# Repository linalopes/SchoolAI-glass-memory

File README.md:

# Glass Memory

A memory game played with the hands, on glass.

Five MDF hands sit on a transparent pane. Four of them hold a lamp. The fifth is Start. A small LED matrix waits, showing a single word. Place a hand on Start, watch the lamps light a sequence, then repeat that sequence by placing your hands on the other four. Each correct round adds one more step. A wrong direction, or a pause that lasts too long, ends the game and returns the panel to waiting.

The electronics stay visible: TRRS cables run across the glass, a custom controller board sits beside the display, and the lamps switch through a relay module. Nothing on the matrix ever names a direction. The sequence exists only as light, then as remembered gesture.

https://github.com/user-attachments/assets/acf82029-6c34-4761-a3db-518c1ffbd78a

---

## How it works

The visitor sees a glass pane with five hand-shaped stations, a red 32×8 LED matrix, and four lamps.

1. The matrix shows **START**.
2. A hand over the Start station begins a game. Start does not light a lamp.
3. The matrix counts **3 · 2 · 1**, then shows the round length as a number.
4. The computer plays the sequence on the four direction lamps only. The display stays blank during playback and never reveals UP, DOWN, LEFT, or RIGHT as text.
5. The matrix shows **GO**. The visitor repeats the sequence on the four direction hands, one press at a time, releasing each hand before the next.
6. A complete correct round shows **OK**. The sequence grows by one random direction and the next round begins.
7. A wrong hand shows **WR**. Taking too long to press, or holding a press too long, shows **TO**. The matrix then shows the number of completed rounds and returns to **START**.

Repeated presses of the same direction count as separate events, as long as the hand is lifted in between. Only Start is accepted while idle; only the four directions are accepted during a turn.

`Start → countdown → watch lamps → GO → repeat → OK → longer sequence`

---

## System overview

```text
Five analog sensors (START, UP, DOWN, LEFT, RIGHT)
        ↓  TRRS cables + adapter boards
Arduino Pro Micro controller
        ↓
Game logic  (sequence, input events, EEPROM calibration)
   ↙                    ↘
MAX7219 matrix         4-channel relay module
(text / numbers)               ↓
                         Direction lamps
```

The controller reads five analog sensor channels, decides when a hand is present, and either plays a lamp sequence or checks the player’s reply. Calibration values live in EEPROM and are loaded at boot; the game firmware does not rewrite them.

---

## Hardware

The running firmware and the KiCad controller project both target a **SparkFun Pro Micro C** (ATmega32U4, [product 15795](https://www.sparkfun.com/products/15795)), socketed on the custom board.

The schematic title block still says “ESP32-S3 controller”. That comment is leftover. The symbol, footprint, pin map, and firmware all use the Pro Micro.

| Role            | What is in this repo                                                                       | Purpose                                     |
| --------------- | ------------------------------------------------------------------------------------------ | ------------------------------------------- |
| Controller      | SparkFun Pro Micro C on the [glass-memory](kicad%20files/glass-memory/) PCB                | Runs calibration or game firmware           |
| Sensor jacks    | Five **PJ-320A** TRRS sockets (START, UP, DOWN, LEFT, RIGHT)                               | Detachable cable to each hand               |
| Sensor adapters | Five [sensor-trrs-adapter-pj320a](kicad%20files/sensor-trrs-adapter-pj320a/) boards        | PJ-320A jack to a 1×4 sensor header         |
| Sensors         | Five analog channels; 4-pin modules with **A0 / D0 / GND / VCC** on the adapter silkscreen | Detect a hand over each station             |
| Display         | External **MAX7219** 4-in-1 matrix (`FC16_HW`, 4 devices → 32×8)                           | Status text and numbers                     |
| Relays          | External **4-channel relay module**, active LOW                                            | Switch the four direction lamps             |
| Power           | 2-pin screw terminal **J8**, “5V Power Source” (pin 1 GND, pin 2 +5V)                      | 5 V rail shared with the Pro Micro `5V` pin |
| Mechanics       | Laser-cut hands / board, 3D-printed hand support and matrix bezel                          | Physical stations on the glass              |

The exact sensor part number is not named in the repository. Firmware comments treat the readings as optical (a slow “ambient optical drift” tracker). The adapter exposes both analog (**A0** / `AO`) and digital (**D0** / `DO`) pins; **only analog is used** by the firmware.

The installation photograph shows filament lamps at the four direction stations. This repository does not document lamp voltage or mains wiring. The relay stage switches those loads; any mains work must follow appropriate electrical safety practice.

### Controller pin map

Verified in both [glass-memory-game.ino](glass-memory-game/glass-memory-game.ino) and [glass-memory-calibration-eeprom.ino](glass-memory-calibration-eeprom/glass-memory-calibration-eeprom.ino), and matched on the Pro Micro footprint in the PCB.

| Function          | Pin |
| ----------------- | --- |
| START sensor      | A10 |
| UP sensor         | A9  |
| DOWN sensor       | A8  |
| LEFT sensor       | A0  |
| RIGHT sensor      | A7  |
| Relay IN1 (UP)    | D5  |
| Relay IN2 (DOWN)  | D4  |
| Relay IN3 (LEFT)  | D3  |
| Relay IN4 (RIGHT) | D2  |
| MAX7219 DIN       | D15 |
| MAX7219 CS        | D14 |
| MAX7219 CLK       | D16 |

Relays are **active LOW** (`RELAY_ON = LOW`). START has no relay.

---

## Custom electronics

Two KiCad 10 projects ship with production gerbers. They are the current hardware, not a paper design only.

### Controller — [kicad files/glass-memory](kicad%20files/glass-memory/)

Silkscreen: *Glass Memory Controller 2026 - v1.0*. Outline **60 × 80 mm** with 2 mm corner radii (`Edge.Cuts` from 50.5,45 to 110.5,125), plus M3 holes.

The board is a hub:

- **U1** — socketed Pro Micro C
- **J1–J5** — PJ-320A TRRS jacks labeled START, UP, DOWN, LEFT, RIGHT
- **J6** — Phoenix MKDS 6-pin screw terminal, “RELAY 4 module”: `RELAY_IN4`, `RELAY_IN3`, `RELAY_IN2`, `RELAY_IN1`, `GND`, `+5V` (pins 1–6)
- **J7** — 5-pin header, “MAX7219 module”: `+5V`, `GND`, `DIN`, `CS`, `CLK` (pins 1–5)
- **J8** — Phoenix MKDS 2-pin screw terminal for 5 V in (pin 1 `GND`, pin 2 `+5V`). There is no on-board regulator; U1 `RAW` is unconnected.

Gerbers: [kicad files/glass-memory/production/](kicad%20files/glass-memory/production/).

### Sensor adapter — [kicad files/sensor-trrs-adapter-pj320a](kicad%20files/sensor-trrs-adapter-pj320a/)

Silkscreen: *TRRS PJ-320A 1×4 ADAPTER*. Schematic comment: *PJ-320A TRRS jack → 1×4 female header*.

One adapter sits at each hand. Board size in the gerber job is **24.6 × 15.1 mm**. The 1×4 header (J1) is:

| Pin | Net   | Back silk |
| --- | ----- | --------- |
| 1   | `AO`  | `A0`      |
| 2   | `DO`  | `D0`      |
| 3   | `GND` | `GND`     |
| 4   | `3V3` | `VCC`     |

Gerbers: [kicad files/sensor-trrs-adapter-pj320a/production/](kicad%20files/sensor-trrs-adapter-pj320a/production/).

---

## Sensor cabling

TRRS (PJ-320A, 3.5 mm 4-pole) is used so each hand can be a remote node: power, ground, and analog return travel in one detachable cable from the glass to the hub.

The table below follows the **PCB copper** on both boards (and the matching gerbers), using the custom [TRRS-PJ-320A](kicad%20files/glass-memory/TRRS-PJ-320A.pretty/TRRS-PJ-320A.kicad_mod) footprint labels.

| TRRS contact | Symbol pin | Controller PCB | Adapter PCB                    |
| ------------ | ---------- | -------------- | ------------------------------ |
| Sleeve       | S / pad 1  | `GND`          | `GND`                          |
| Tip          | T / pad 2  | not connected  | `DO` (digital out)             |
| Ring 1       | R1 / pad 3 | `+5V`          | net labeled `3V3` / silk `VCC` |
| Ring 2       | R2 / pad 4 | analog `*_A0`  | `AO`                           |

The controller uses **three** conductors. Tip is unused on the hub, so the sensor digital output is not read.

**Ambiguities to be aware of:**

1. The hub schematic *labels* next to the jacks appear to swap Sleeve and Ring 1 relative to the PCB (`+5V` on Sleeve, `GND` on Ring 1). The PCB, gerbers, and adapter all agree the other way: Sleeve = ground, Ring 1 = power. This README follows the copper.
2. The hub puts **+5 V** on Ring 1. The adapter net for that same contact is named **3V3**. Confirm the sensor module’s supply rating before applying power. TODO: document the intended sensor supply and module part number.

---

## Sensors

Five analog inputs, mapped as START / UP / DOWN / LEFT / RIGHT.

Each reading is an average of four ADC samples (first conversion after a channel change is discarded), then exponentially smoothed (`75%` previous + `25%` new). Presence is not a raw threshold. After calibration, a score of `0%` is the resting baseline and `100%` is the stored hand sample:

- press when score ≥ **50%** and that sensor beats the next by **10%**
- release when score < **30%**
- a press must stay stable **80 ms**; after release, the allowed sensors must stay neutral **120 ms** before the next press can arm

During a player turn the RAM baseline slowly follows ambient optical drift (every 100 ms, only while a sensor is well below the press threshold). EEPROM is not updated. The useful span is not allowed to collapse below a live delta of 20.

The game firmware latches one accepted sensor until *that same* sensor releases, so LEFT → LEFT is two events if the hand lifts in between.

---

## Calibration

Firmware: [glass-memory-calibration-eeprom/glass-memory-calibration-eeprom.ino](glass-memory-calibration-eeprom/glass-memory-calibration-eeprom.ino)

Optical rest levels shift with light and mounting. Calibration measures a clear-pane baseline and a hand sample per station, stores both in EEPROM, and is a **separate sketch** from the game.

Upload this sketch to the Pro Micro (Arduino IDE, board: SparkFun Pro Micro / ATmega32U4). Serial is 115200 baud. Calibration still runs if Serial is not open.

### Automatic flow

The matrix and Serial walk through the same sequence:

```text
CAL
CLEAR   → keep the complete sensor area clear → 3 · 2 · 1 → baseline
START   → prepare a hand over START → 3 · 2 · 1 → hand sample
UP      → same
DOWN
LEFT
RIGHT
DONE    → values written to EEPROM
TEST    → live sensor + relay check
```

Each measurement averages **120** analog samples with **4 ms** between samples. For every sensor the sketch stores:

- `baseline` — mean of the clear-pane capture
- `hand` — mean of that station’s hand capture
- `delta` — `hand − baseline`

Min/max during each capture are printed for noise diagnosis. The EEPROM record is:

```text
magic 0x474D ("GM") · version 1 · baseline[5] · hand[5] · checksum
```

The write is read back immediately (`EEPROM SAVE: OK` or `ERROR`). Values persist across power cycles. Resetting the board runs the whole calibration again.

### Live test

After SAVE, the sketch stays in TEST. An accepted sensor lights its relay (except START) and draws a marker on the matrix (center / top / bottom / left / right edge). Serial prints all five `filtered/score%` values twice a second, tagged `[ACTIVE]`, `[CAND]`, or `[--]`.

Send `P` on Serial to reprint the calibration table.

Then upload the game sketch. Do not recalibrate unless the mounting or lighting changed.

---

## Firmware

Current game firmware: [glass-memory-game/glass-memory-game.ino](glass-memory-game/glass-memory-game.ino) (**Game V4**).

It is not the calibration sketch. If EEPROM magic, version, checksum, or any sensor delta is invalid (`|delta| < 2`), the matrix shows **CAL** and the board waits there.

V4 responsibilities:

- load calibration; never write EEPROM
- continuous analog filter; slow RAM baseline tracking
- PRESS → LATCH → RELEASE → NEUTRAL → ARMED input machine
- idle wait on START only
- random direction sequence (UP/DOWN/LEFT/RIGHT), length 1…32
- lamp-only playback (`700 ms` on, `250 ms` gap)
- per-press timeout `10 s`, release timeout `5 s`
- player lamp feedback while the accepted hand is present (`PLAYER_LAMP_FEEDBACK`; set to `0` only for A/B diagnostics — computer playback always uses the lamps)
- serial debug at 115200 when `DEBUG_SERIAL` is 1

---

## Display

A four-module MAX7219 chain (`MD_MAX72XX::FC16_HW`, intensity 3). Firmware maps pixels with **X reversed** and **Y normal** (`physicalCol = 31 − logicalCol`) so the physical panel matches the intended left-to-right text.

| When                | Matrix shows             |
| ------------------- | ------------------------ |
| Idle                | `START`                  |
| Missing calibration | `CAL` (then halt)        |
| New game            | `3` `2` `1`              |
| Before playback     | round length as a number |
| Sequence playback   | blank                    |
| Player turn         | `GO`                     |
| Round correct       | `OK`                     |
| Wrong hand          | `WR`, then the score     |
| Timeout             | `TO`, then the score     |

The 3D-printed [MAX7219 bezel](3D%20print%20files/glass_memory_max7219_beze.scad) is a rear-entry frame for a 32×8 assembly (~131 mm wide including inter-module gaps).

---

## Relays and lights

Four channels, active LOW, mapped as IN1–IN4 above. During computer playback each step turns on exactly one lamp. During the player turn the matching lamp stays on while that hand remains present (if player feedback is enabled). START never drives a relay. All relays are forced off between steps, on error, and in idle.

---

## Building the system

1. Fabricate the controller and one adapter per sensor (gerbers are under each project’s `production/` folder).
2. Seat the Pro Micro in the U1 socket.
3. Wire the MAX7219 module to J7 and the 4-channel relay module to J6.
4. At each hand, plug the 4-pin sensor into the adapter header and a TRRS cable from the adapter jack to the matching hub jack.
5. Supply 5 V on J8. Confirm sensor supply (see cabling note on +5 V vs `3V3`).
6. Upload **calibration**, clear the pane, then present a hand at each named station.
7. In TEST, confirm each direction lights the intended lamp and that Serial scores separate cleanly.
8. Upload **game** firmware. If the matrix shows `CAL`, calibration is missing or invalid — go back to step 6.
9. From idle, start a game and walk a short sequence before hanging the piece.

Laser-cut hands and board: [laser cut files](laser%20cut%20files/) (72 dpi SVG, plus `board.af`). 3D-printed hand support and matrix bezel: [3D print files](3D%20print%20files/). The hand OpenSCAD file is generated from the 72 dpi SVG contour (hand size ~60 × 80 mm, 3 mm MDF).

---

## Repository structure

```text
.
├── README.md
├── glass-memory.webp                          installation photograph
├── glass-memory.mp4                           installation video
├── glass-memory-game/                         game firmware V4
│   └── glass-memory-game.ino
├── glass-memory-calibration-eeprom/           EEPROM calibration + live TEST
│   └── glass-memory-calibration-eeprom.ino
├── kicad files/
│   ├── glass-memory/                          controller PCB + gerbers
│   └── sensor-trrs-adapter-pj320a/            per-sensor TRRS adapter + gerbers
├── laser cut files/                           hands, start hand, board (SVG / Affinity)
└── 3D print files/                            hand support + MAX7219 bezel
```

KiCad local history and zip backups exist under the hardware folders; they are snapshots, not the working design.

---

## Troubleshooting

Drawn from the diagnostic paths that actually exist in firmware.

| Symptom                                              | What the firmware is telling you                                                                                               |
| ---------------------------------------------------- | ------------------------------------------------------------------------------------------------------------------------------ |
| Matrix stuck on `CAL`                                | EEPROM magic/version/checksum failed, or a stored delta is ~0. Run calibration and confirm `EEPROM SAVE: OK`.                  |
| Start does nothing, directions work (or the reverse) | Wrong TRRS jack, or the allowed-sensor mask: idle listens only to START; play listens only to the four directions.             |
| One press counted twice, or LEFT cannot follow LEFT  | The hand never returned below the 30% release score for 120 ms. Check Serial scores in the calibration TEST.                   |
| Wrong lamp or two lamps                              | Winner margin is 10%. If two sensors both cross 50%, no winner is taken. Recalibrate with only one hand in place.              |
| Resting scores creep up after a while                | Expected: game tracks ambient drift in RAM only. If a real touch no longer reaches ~100%, recalibrate.                         |
| Display text mirrored                                | Firmware already reverses X for this panel. If it looks wrong, the module order or `FC16_HW` wiring does not match this build. |
| Relays on when they should be off                    | Modules are active LOW. Confirm the board is not treating IN as active HIGH.                                                   |
| `TO` during play                                     | 10 s to make the next press, or 5 s to release.                                                                                |
| Calibration deltas tiny                              | Baseline and hand samples were too similar. Repeat CLEAR with the pane empty, then place the hand fully over that station.     |

Serial (both sketches, 115200) prints per-sensor scores when debug is on. Calibration TEST is the right place to watch `base` / `hand` / `delta` / `noise`.

---

## Software requirements

- Arduino IDE (or any environment that can flash a Pro Micro / ATmega32U4)
- Libraries referenced by `#include`: **MD_MAX72xx**, **SPI**, **EEPROM** (SPI and EEPROM are Arduino core libraries). No versions are pinned in this repo.
- **KiCad 10** (schematic `generator_version "10.0"`)
- **OpenSCAD**, if regenerating the 3D parts

---

## Glass Memory web app

This repository does not contain a web app, simulator, or networked companion. The installation runs entirely on the Pro Micro.

TODO: link a companion app here if it lives in another repo.

---

## About the project

Glass Memory is an embodied memory game: instructions arrive as lamps on glass, and the reply is a sequence of hands. The matrix is deliberately mute about direction. What you remember is a path of gestures, not a string of arrows.

The work sits in physical computing — analog optical sensing, a visible cable plant, calibration as a ritual of settling the pane to a room — rather than a hidden black-box kiosk.

PCB silkscreen: *heavily inspired by Nathan Rabinovitch*. No exhibition history is recorded in this repository.

---

## Credits

- **Lina Lopes** — School of Tomorrow's AI (controller and adapter silkscreen, 2026 v1.0)
- Inspired by **Nathan Rabinovitch**

TODO: license. No `LICENSE` file is present in this repository.

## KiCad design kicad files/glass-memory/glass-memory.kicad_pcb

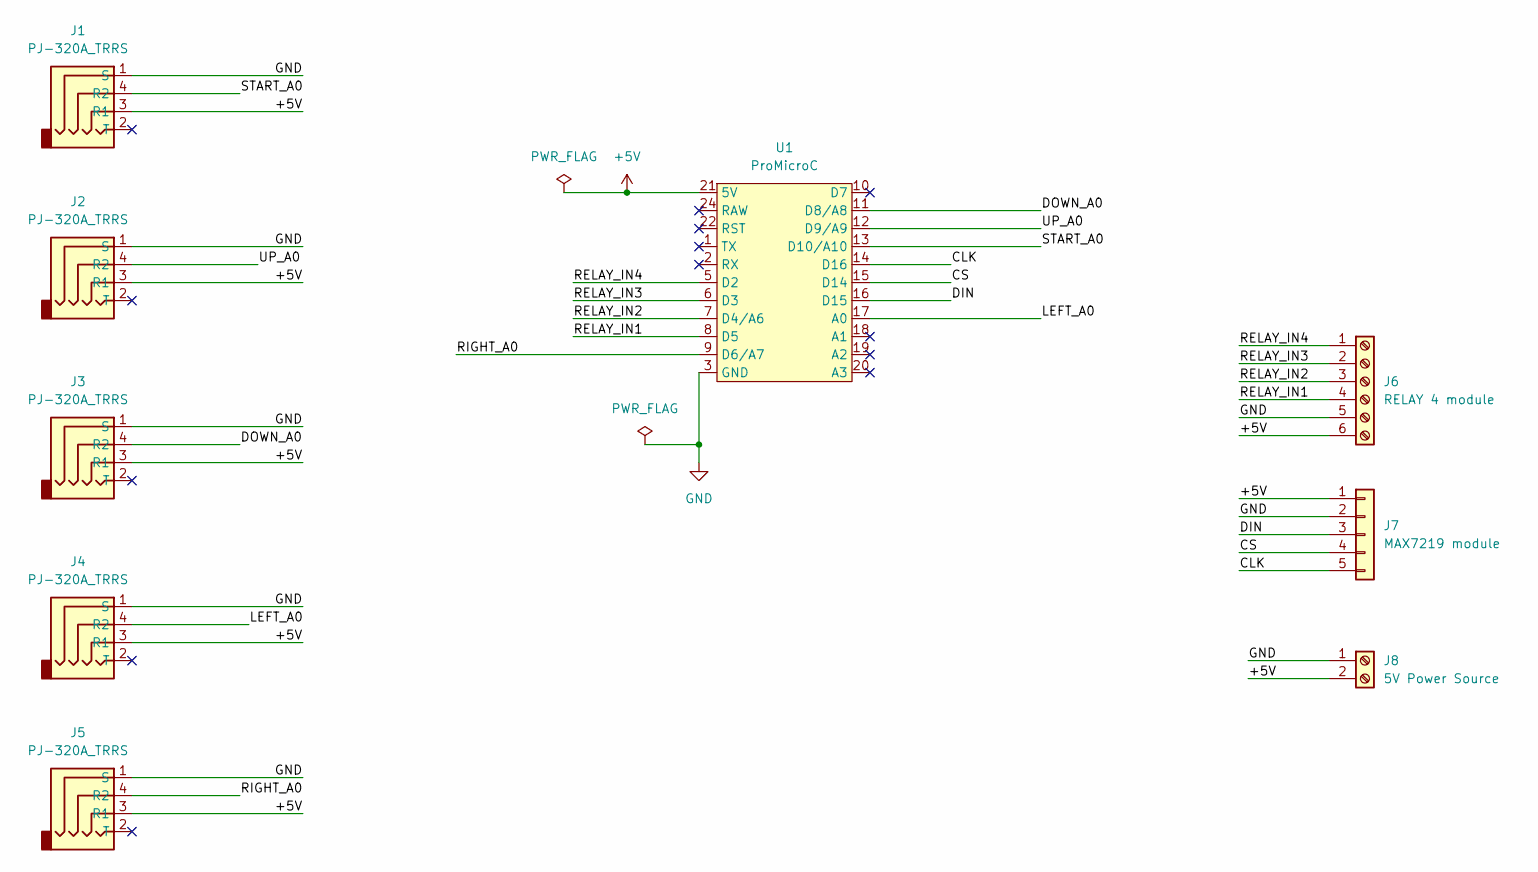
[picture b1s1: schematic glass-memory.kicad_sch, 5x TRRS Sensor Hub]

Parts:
J1, J2, J3, J4, J5: PJ-320A_TRRS; TRRS-PJ-320A
J6: RELAY 4 module; TerminalBlock_Phoenix_MKDS-1,5-6-5.08_1x06_P5.08mm_Horizont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
J7: MAX7219 module; PinHeader_1x05_P2.54mm_Vertical
J8: 5V Power Source; TerminalBlock_Phoenix_MKDS-1,5-2-5.08_1x02_P5.08mm_Horizont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
U1: ProMicroC; ProMicroC-socketed

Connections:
+5V: J1.3 (R1), J2.3 (R1), J3.3 (R1), J4.3 (R1), J5.3 (R1), J6.6, J7.1, J8.2, U1.21 (5V)
/CLK: J7.5, U1.14 (D16)
/CS: J7.4, U1.15 (D14)
/DIN: J7.3, U1.16 (D15)
/DOWN_A0: J3.4 (R2), U1.11 (D8/A8)
/LEFT_A0: J4.4 (R2), U1.17 (A0)
/RELAY_IN1: J6.4, U1.8 (D5)
/RELAY_IN2: J6.3, U1.7 (D4/A6)
/RELAY_IN3: J6.2, U1.6 (D3)
/RELAY_IN4: J6.1, U1.5 (D2)
/RIGHT_A0: J5.4 (R2), U1.9 (D6/A7)
/START_A0: J1.4 (R2), U1.13 (D10/A10)
/UP_A0: J2.4 (R2), U1.12 (D9/A9)
GND: J1.1 (S), J2.1 (S), J3.1 (S), J4.1 (S), J5.1 (S), J6.5, J7.2, J8.1, U1.3 (GND), U1.4 (GND), U1.23 (GND)

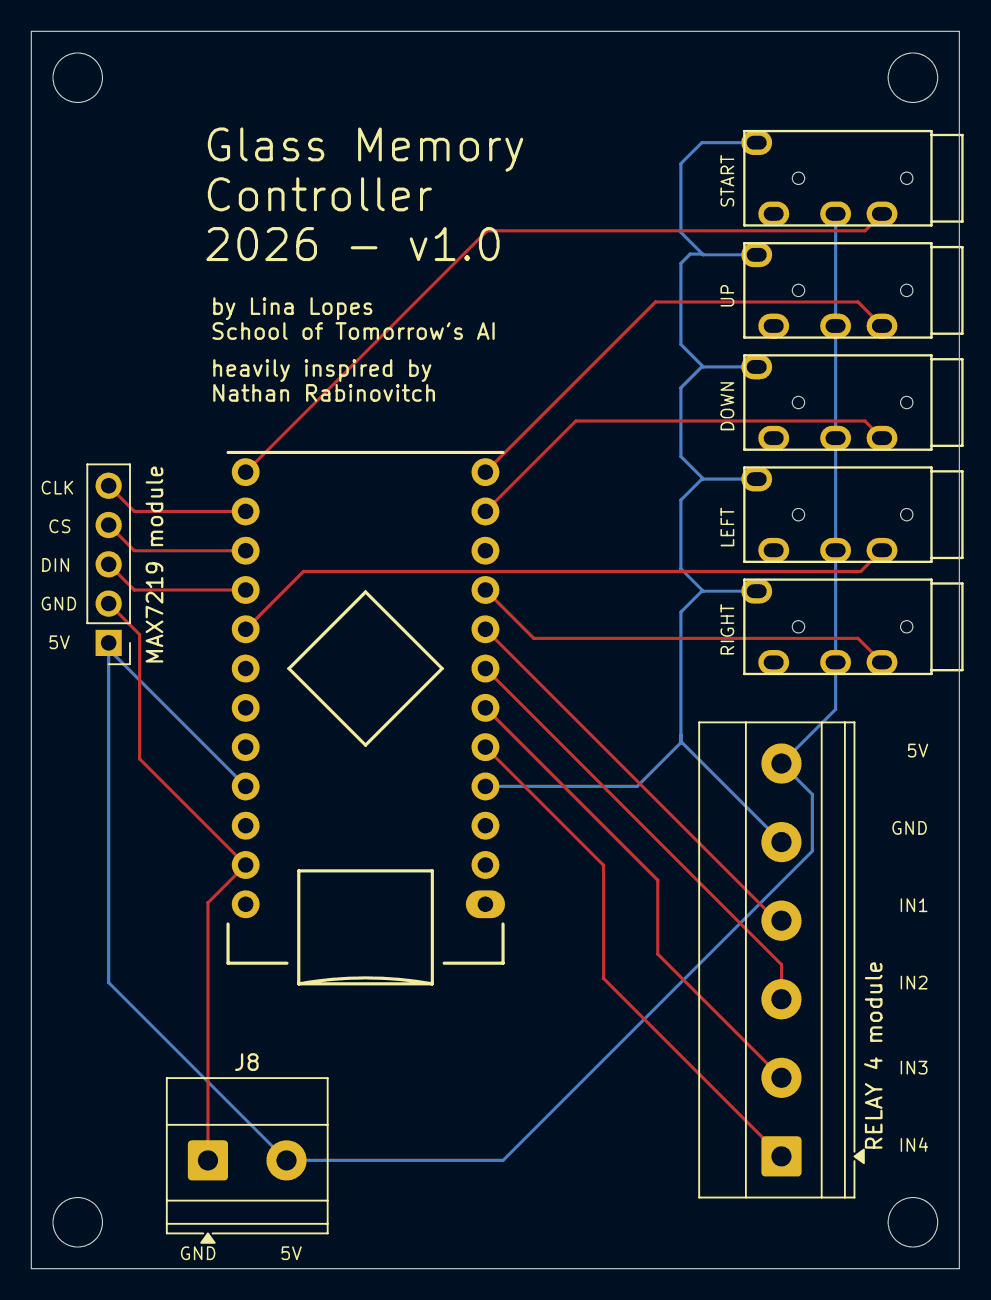
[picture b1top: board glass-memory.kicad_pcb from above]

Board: 2 copper layers, 60.0 x 80.0 mm, 9 parts (0 on the bottom side), 14 nets.
